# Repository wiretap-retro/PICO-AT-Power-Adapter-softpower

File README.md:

# PICO-AT Power Adapter - softpower version
A version of the regular PICO-AT adapter, but with momentary power switch support.

## Intro
I designed this board for a small SBC that I could not fit a large power supply in the enclosure. This design is recommended for PICO-PSU units, and can be used with various retro motherboards that have the AT-style power connector. It is not recommended to pass sustained high current over 8-amps on any single power rail through this PCB. This version utilizes a power switch with momentary actuation. 

## Building
* Detailed BOM for Mouser parts is included. Subsitutions may be necessary depending on the chip/component shortages.
* Solder the SMD components first, then solder the through-hole components. The 7905 component will need to be flush clipped with the board before soldering, to ensure the ATX connector sits flat.
* Depending on your motherboard, this may not fit without modification to the motherboard's power connector. You will need to have the square pins on the power connector, not the larger round pins or flat pins. Most AT boards have the flat pins. See notes section below.

## Notes
* Molex only produced the flat style AT pin header (8619) for use with the 90331 power supply connectors. The flat pin 8619 style motherboard side connectors were only used on AT motherboards to a certain time period, then Molex discontinued the 8619 and replaced it with the KK 396 square pin connector, which is compatible with the 90331 connector as well as KK 396 female connectors, obviously. I only have one motherboard in my collection that came standard with the KK 396 connector. If the motherboard uses the old 8619 connector, it would need to be replaced with the KK 396 type. So, with the KK 396 compatible with both the 90331 and KK 396 itself, you lose no functionality with an original AT power supply connector. I have validated this with motherboards I have converted. The part number for the motherboard side is Molex 41791-0836. (2 required)
* The power switch pin header is for connecting a standard momentary switch to control the ATX power supply's on/off state. You can wire it to your ATX case's power switch. The Maxim MAX16054 chip controls the power on/off state. One press for on, one press for off, with debounce integrated.

## Community Works
Check out Vogons.org for the thread where people are building these and also modifying the design to have fan headers and other cool stuff: https://www.vogons.org/viewtopic.php?f=46&t=86465

## Other
This is an open source design. Feel free to do what you want with it.

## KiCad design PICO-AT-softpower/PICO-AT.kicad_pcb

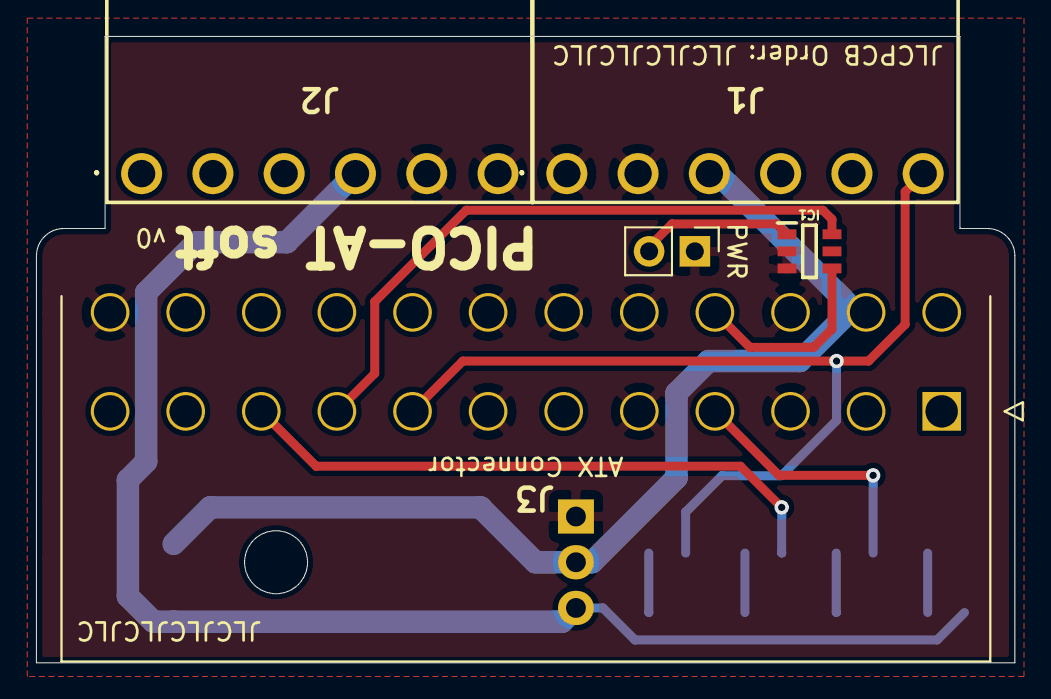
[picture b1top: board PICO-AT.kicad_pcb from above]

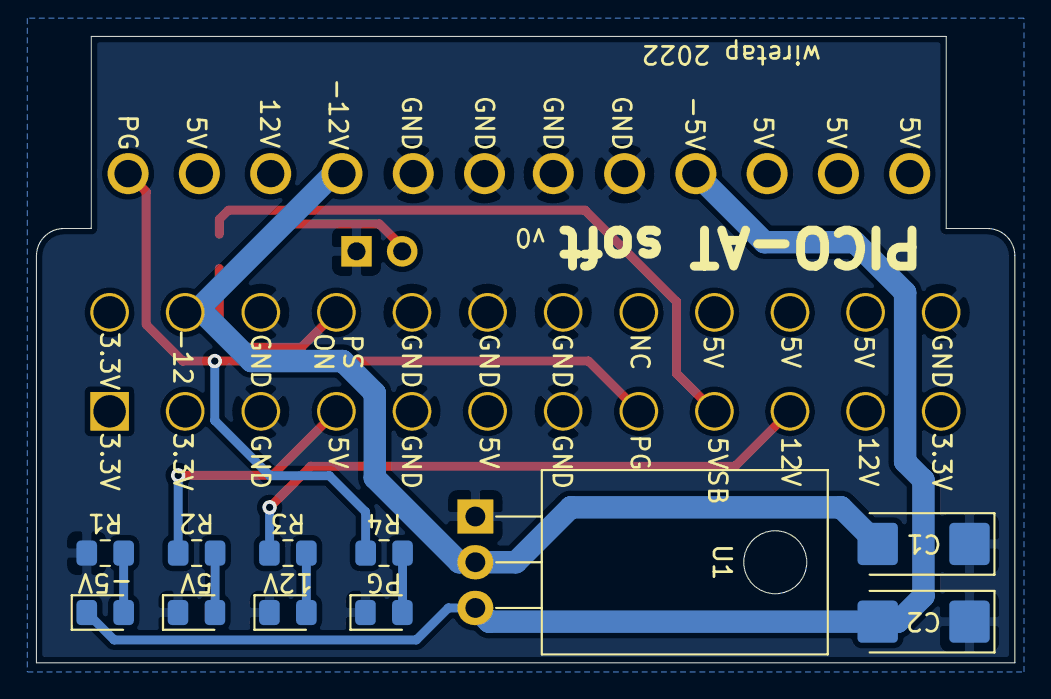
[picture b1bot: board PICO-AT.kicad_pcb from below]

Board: 4 copper layers, 54.4 x 34.8 mm, 16 parts (11 on the bottom side), 14 nets.

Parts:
5V, 12V: LED; LED_0805_2012Metric_Pad1.15x1.40mm_HandSolder
-5V: LED; LED_0805_2012Metric_Pad1.15x1.40mm_HandSolder
C1: 2.2uF; CP_EIA-6032-28_Kemet-C_Pad2.25x2.35mm_HandSolder
C2: 1uF; CP_EIA-6032-28_Kemet-C_Pad2.25x2.35mm_HandSolder
IC1: MAX16054AZT+T; SOT95P275X110-6N
J1, J2: 09-48-1064; 09481064
J3: 87427-2402
PG: LED; LED_0805_2012Metric_Pad1.15x1.40mm_HandSolder
PWR: PWR_SW; PinHeader_1x02_P2.54mm_Vertical
R1, R2, R4: 330; R_0805_2012Metric_Pad1.15x1.40mm_HandSolder
R3: 1k; R_0805_2012Metric_Pad1.15x1.40mm_HandSolder
U1: L7905; TO-220-3_Horizontal_TabDown

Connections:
/3.3V: J3.1, J3.2, J3.12, J3.13
/5V: J1.5, J2.1, J2.2, J2.3, J3.4, J3.6, J3.21, J3.22, J3.23, R2.1
/5VSB: IC1.6, J3.9
/12V: J1.4, J3.10, J3.11, R3.1
/-5V: -5V.1, C2.2, J2.4, U1.3
/-12V: C1.2, J1.3, J3.14, U1.2
/GND: 5V.1, 12V.1, C1.1, C2.1, IC1.2, IC1.3, J1.1, J1.2, J2.5, J2.6, J3.3, J3.5, J3.7, J3.15, J3.17, J3.18, J3.19, J3.24, PG.1, PWR.1, R1.1, U1.1
/PG: J1.6, J3.8, R4.1
/PS-ON: IC1.4, J3.16
unnamed: -5V.2, R1.2
unnamed: 5V.2, R2.2
unnamed: 12V.2, R3.2
unnamed: PG.2, R4.2
unnamed: IC1.1, PWR.2
